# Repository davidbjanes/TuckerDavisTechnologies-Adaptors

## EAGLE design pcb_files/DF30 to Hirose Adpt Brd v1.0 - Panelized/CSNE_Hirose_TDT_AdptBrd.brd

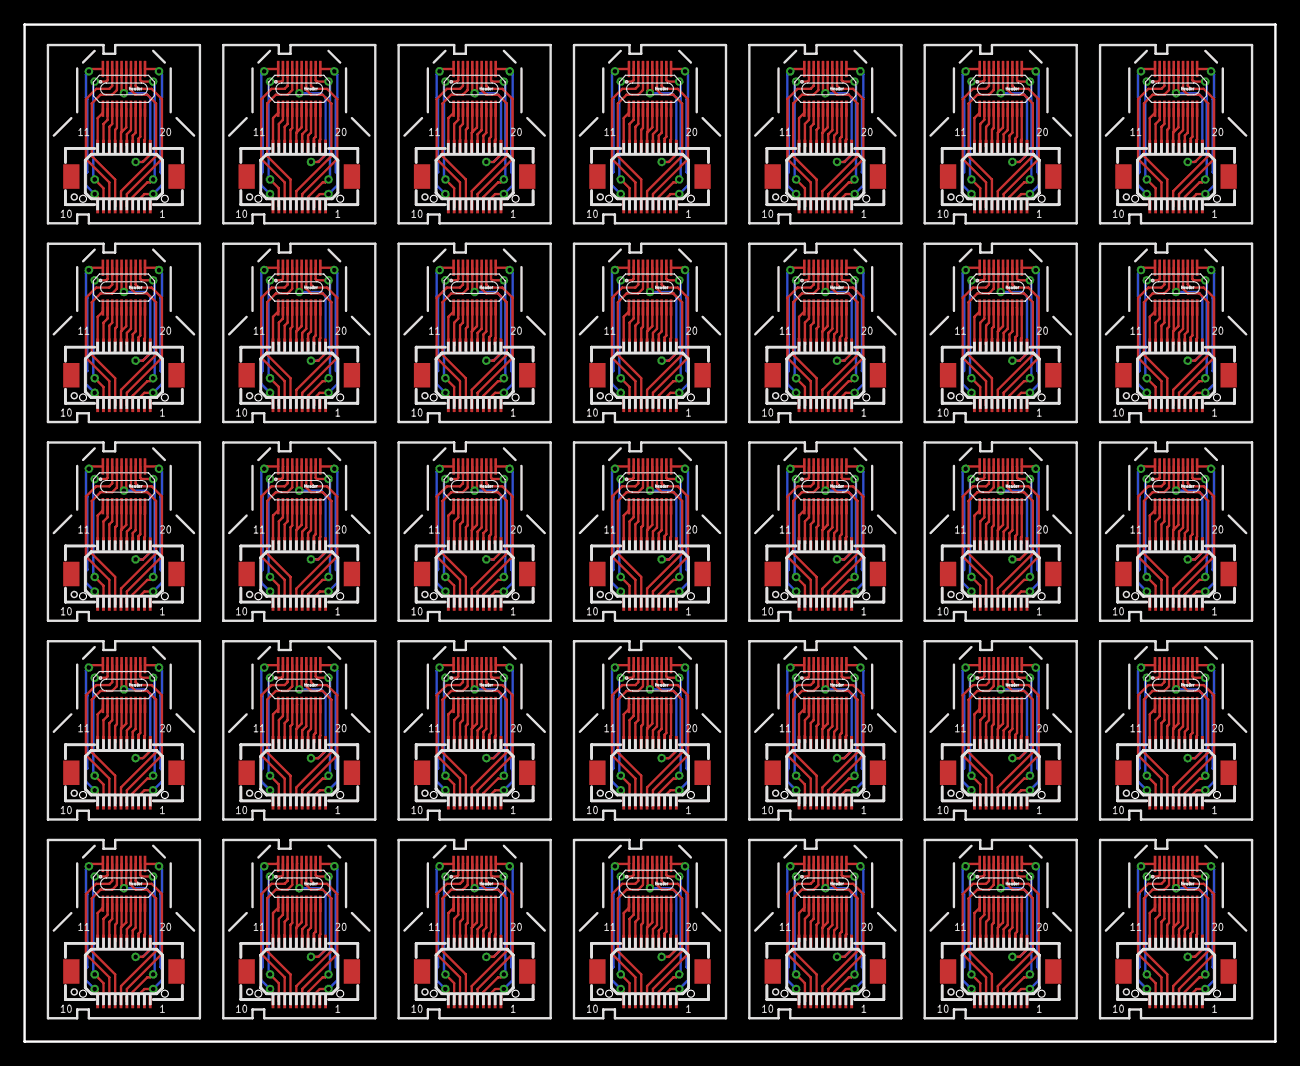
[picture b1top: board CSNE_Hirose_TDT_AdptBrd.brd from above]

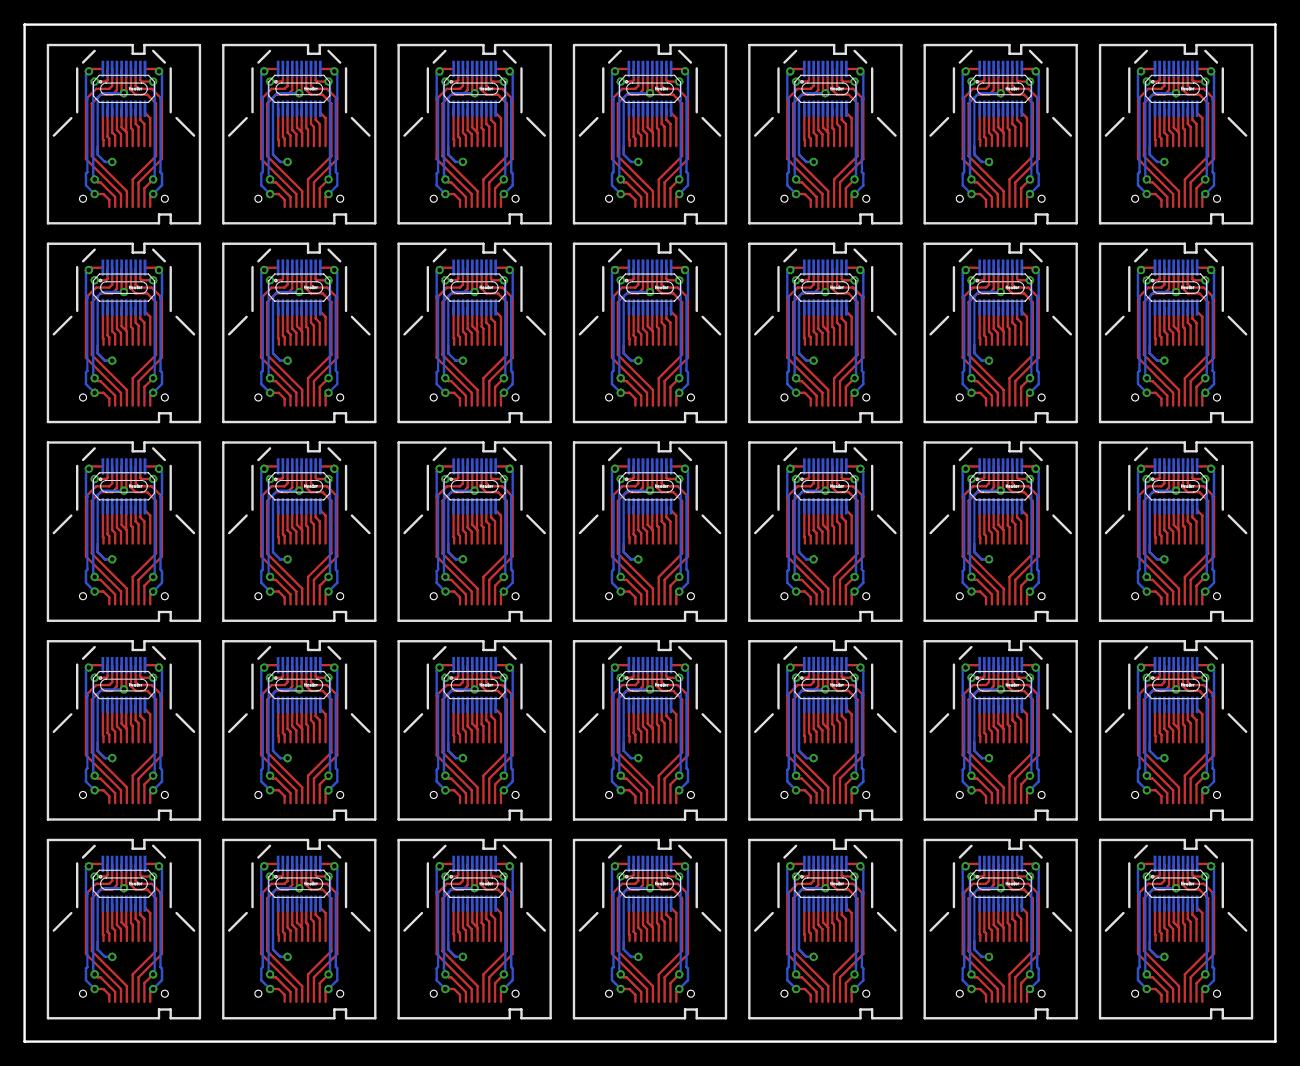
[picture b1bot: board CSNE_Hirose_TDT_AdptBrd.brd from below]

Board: 4 copper layers, 107.0 x 87.0 mm, 105 parts (35 on the bottom side), 630 nets.

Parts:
U$1, U$2, U$4, U$5, U$7, U$8, U$10, U$11, U$13, U$14, U$16, U$17, U$19, U$20, U$22, U$23, U$25, U$26, U$28, U$29, U$31, U$32, U$34, U$35, U$37, U$38, U$40, U$41, U$43, U$44, U$46, U$47, U$49, U$50, U$52, U$53, U$55, U$56, U$58, U$59, U$61, U$62, U$64, U$65, U$67, U$68, U$70, U$71, U$73, U$74, U$76, U$77, U$79, U$80, U$82, U$83, U$85, U$86, U$88, U$89, U$91, U$92, U$94, U$95, U$97, U$98, U$100, U$101, U$103, U$104: DF30_HEADER; DF30FC-20DP-0.4V
U$3, U$6, U$9, U$12, U$15, U$18, U$21, U$24, U$27, U$30, U$33, U$36, U$39, U$42, U$45, U$48, U$51, U$54, U$57, U$60, U$63, U$66, U$69, U$72, U$75, U$78, U$81, U$84, U$87, U$90, U$93, U$96, U$99, U$102, U$105: CON-DF17-20F

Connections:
unnamed: U$1.P$1, U$3.1
unnamed: U$1.P$2, U$3.3
unnamed: U$1.P$3, U$3.5
unnamed: U$1.P$4, U$3.7
unnamed: U$1.P$5, U$1.P$6, U$3.20
unnamed: U$1.P$7, U$3.9
unnamed: U$1.P$8, U$3.11
unnamed: U$1.P$9, U$3.13
unnamed: U$1.P$10, U$3.15
unnamed: U$1.P$11, U$3.18
unnamed: U$1.P$12, U$3.16
unnamed: U$1.P$13, U$3.14
unnamed: U$1.P$14, U$3.12
unnamed: U$5.P$1, U$6.1
unnamed: U$1.P$15, U$1.P$16, U$3.10
unnamed: U$1.P$17, U$3.8
unnamed: U$1.P$18, U$3.6
unnamed: U$1.P$19, U$3.4
unnamed: U$1.P$20, U$3.2
unnamed: U$5.P$2, U$6.3
unnamed: U$5.P$3, U$6.5
unnamed: U$5.P$4, U$6.7
unnamed: U$5.P$5, U$5.P$6, U$6.20
unnamed: U$5.P$7, U$6.9
unnamed: U$5.P$8, U$6.11
unnamed: U$5.P$9, U$6.13
unnamed: U$5.P$10, U$6.15
unnamed: U$5.P$11, U$6.18
unnamed: U$5.P$12, U$6.16
unnamed: U$5.P$13, U$6.14
unnamed: U$5.P$14, U$6.12
unnamed: U$5.P$15, U$5.P$16, U$6.10
unnamed: U$5.P$17, U$6.8
unnamed: U$5.P$18, U$6.6
unnamed: U$5.P$19, U$6.4
unnamed: U$5.P$20, U$6.2
unnamed: U$8.P$1, U$9.1
unnamed: U$8.P$2, U$9.3
unnamed: U$8.P$3, U$9.5
unnamed: U$8.P$4, U$9.7
unnamed: U$8.P$5, U$8.P$6, U$9.20
unnamed: U$8.P$7, U$9.9
unnamed: U$8.P$8, U$9.11
unnamed: U$8.P$9, U$9.13
unnamed: U$8.P$10, U$9.15
unnamed: U$8.P$11, U$9.18
unnamed: U$8.P$12, U$9.16
unnamed: U$8.P$13, U$9.14
unnamed: U$8.P$14, U$9.12
unnamed: U$8.P$15, U$8.P$16, U$9.10
unnamed: U$8.P$17, U$9.8
unnamed: U$8.P$18, U$9.6
unnamed: U$8.P$19, U$9.4
unnamed: U$8.P$20, U$9.2
unnamed: U$11.P$1, U$12.1
unnamed: U$11.P$2, U$12.3
unnamed: U$11.P$3, U$12.5
unnamed: U$11.P$4, U$12.7
unnamed: U$11.P$5, U$11.P$6, U$12.20
unnamed: U$11.P$7, U$12.9
unnamed: U$11.P$8, U$12.11
unnamed: U$11.P$9, U$12.13
unnamed: U$11.P$10, U$12.15
unnamed: U$11.P$11, U$12.18
unnamed: U$11.P$12, U$12.16
unnamed: U$11.P$13, U$12.14
unnamed: U$11.P$14, U$12.12
unnamed: U$11.P$15, U$11.P$16, U$12.10
unnamed: U$11.P$17, U$12.8
unnamed: U$11.P$18, U$12.6
unnamed: U$11.P$19, U$12.4
unnamed: U$11.P$20, U$12.2
unnamed: U$14.P$1, U$15.1
unnamed: U$14.P$2, U$15.3
unnamed: U$14.P$3, U$15.5
unnamed: U$14.P$4, U$15.7
unnamed: U$14.P$5, U$14.P$6, U$15.20
unnamed: U$14.P$7, U$15.9
unnamed: U$14.P$8, U$15.11
unnamed: U$14.P$9, U$15.13
unnamed: U$14.P$10, U$15.15
unnamed: U$14.P$11, U$15.18
unnamed: U$14.P$12, U$15.16
unnamed: U$14.P$13, U$15.14
unnamed: U$14.P$14, U$15.12
unnamed: U$14.P$15, U$14.P$16, U$15.10
unnamed: U$14.P$17, U$15.8
unnamed: U$14.P$18, U$15.6
unnamed: U$14.P$19, U$15.4
unnamed: U$14.P$20, U$15.2
unnamed: U$17.P$1, U$18.1
unnamed: U$17.P$2, U$18.3
unnamed: U$17.P$3, U$18.5
unnamed: U$17.P$4, U$18.7
unnamed: U$17.P$5, U$17.P$6, U$18.20
unnamed: U$17.P$7, U$18.9
unnamed: U$17.P$8, U$18.11
unnamed: U$17.P$9, U$18.13
unnamed: U$17.P$10, U$18.15
unnamed: U$17.P$11, U$18.18
unnamed: U$17.P$12, U$18.16
unnamed: U$17.P$13, U$18.14
unnamed: U$17.P$14, U$18.12
unnamed: U$17.P$15, U$17.P$16, U$18.10
unnamed: U$17.P$17, U$18.8
unnamed: U$17.P$18, U$18.6
unnamed: U$17.P$19, U$18.4
unnamed: U$17.P$20, U$18.2
unnamed: U$20.P$1, U$21.1
unnamed: U$20.P$2, U$21.3
unnamed: U$20.P$3, U$21.5
unnamed: U$20.P$4, U$21.7
unnamed: U$20.P$5, U$20.P$6, U$21.20
unnamed: U$20.P$7, U$21.9
unnamed: U$20.P$8, U$21.11
unnamed: U$20.P$9, U$21.13
unnamed: U$20.P$10, U$21.15
unnamed: U$20.P$11, U$21.18
unnamed: U$20.P$12, U$21.16
unnamed: U$20.P$13, U$21.14
unnamed: U$20.P$14, U$21.12
unnamed: U$20.P$15, U$20.P$16, U$21.10
unnamed: U$20.P$17, U$21.8
unnamed: U$20.P$18, U$21.6
unnamed: U$20.P$19, U$21.4
unnamed: U$20.P$20, U$21.2
unnamed: U$23.P$1, U$24.1
unnamed: U$23.P$2, U$24.3
unnamed: U$23.P$3, U$24.5
unnamed: U$23.P$4, U$24.7
unnamed: U$23.P$5, U$23.P$6, U$24.20
unnamed: U$23.P$7, U$24.9
unnamed: U$23.P$8, U$24.11
unnamed: U$23.P$9, U$24.13
unnamed: U$23.P$10, U$24.15
unnamed: U$23.P$11, U$24.18
unnamed: U$23.P$12, U$24.16
unnamed: U$23.P$13, U$24.14
unnamed: U$23.P$14, U$24.12
unnamed: U$23.P$15, U$23.P$16, U$24.10
unnamed: U$23.P$17, U$24.8
unnamed: U$23.P$18, U$24.6
unnamed: U$23.P$19, U$24.4
unnamed: U$23.P$20, U$24.2
unnamed: U$26.P$1, U$27.1
unnamed: U$26.P$2, U$27.3
unnamed: U$26.P$3, U$27.5
unnamed: U$26.P$4, U$27.7
unnamed: U$26.P$5, U$26.P$6, U$27.20
unnamed: U$26.P$7, U$27.9
unnamed: U$26.P$8, U$27.11
unnamed: U$26.P$9, U$27.13
unnamed: U$26.P$10, U$27.15
unnamed: U$26.P$11, U$27.18
unnamed: U$26.P$12, U$27.16
unnamed: U$26.P$13, U$27.14
unnamed: U$26.P$14, U$27.12
unnamed: U$26.P$15, U$26.P$16, U$27.10
unnamed: U$26.P$17, U$27.8
unnamed: U$26.P$18, U$27.6
unnamed: U$26.P$19, U$27.4
unnamed: U$26.P$20, U$27.2
unnamed: U$29.P$1, U$30.1
unnamed: U$29.P$2, U$30.3
unnamed: U$29.P$3, U$30.5
unnamed: U$29.P$4, U$30.7
unnamed: U$29.P$5, U$29.P$6, U$30.20
unnamed: U$29.P$7, U$30.9
unnamed: U$29.P$8, U$30.11
unnamed: U$29.P$9, U$30.13
unnamed: U$29.P$10, U$30.15
unnamed: U$29.P$11, U$30.18
unnamed: U$29.P$12, U$30.16
unnamed: U$29.P$13, U$30.14
unnamed: U$29.P$14, U$30.12
unnamed: U$29.P$15, U$29.P$16, U$30.10
unnamed: U$29.P$17, U$30.8
unnamed: U$29.P$18, U$30.6
unnamed: U$29.P$19, U$30.4
unnamed: U$29.P$20, U$30.2
unnamed: U$32.P$1, U$33.1
unnamed: U$32.P$2, U$33.3
unnamed: U$32.P$3, U$33.5
unnamed: U$32.P$4, U$33.7
unnamed: U$32.P$5, U$32.P$6, U$33.20
unnamed: U$32.P$7, U$33.9
unnamed: U$32.P$8, U$33.11
unnamed: U$32.P$9, U$33.13
unnamed: U$32.P$10, U$33.15
unnamed: U$32.P$11, U$33.18
unnamed: U$32.P$12, U$33.16
unnamed: U$32.P$13, U$33.14
unnamed: U$32.P$14, U$33.12
unnamed: U$32.P$15, U$32.P$16, U$33.10
unnamed: U$32.P$17, U$33.8
unnamed: U$32.P$18, U$33.6
unnamed: U$32.P$19, U$33.4
unnamed: U$32.P$20, U$33.2
unnamed: U$35.P$1, U$36.1
unnamed: U$35.P$2, U$36.3
unnamed: U$35.P$3, U$36.5
unnamed: U$35.P$4, U$36.7
unnamed: U$35.P$5, U$35.P$6, U$36.20
unnamed: U$35.P$7, U$36.9
unnamed: U$35.P$8, U$36.11
unnamed: U$35.P$9, U$36.13
unnamed: U$35.P$10, U$36.15
unnamed: U$35.P$11, U$36.18
unnamed: U$35.P$12, U$36.16
unnamed: U$35.P$13, U$36.14
unnamed: U$35.P$14, U$36.12
unnamed: U$35.P$15, U$35.P$16, U$36.10
unnamed: U$35.P$17, U$36.8
unnamed: U$35.P$18, U$36.6
unnamed: U$35.P$19, U$36.4
unnamed: U$35.P$20, U$36.2
unnamed: U$38.P$1, U$39.1
unnamed: U$38.P$2, U$39.3
unnamed: U$38.P$3, U$39.5
unnamed: U$38.P$4, U$39.7
unnamed: U$38.P$5, U$38.P$6, U$39.20
unnamed: U$38.P$7, U$39.9
unnamed: U$38.P$8, U$39.11
unnamed: U$38.P$9, U$39.13
unnamed: U$38.P$10, U$39.15
unnamed: U$38.P$11, U$39.18
unnamed: U$38.P$12, U$39.16
unnamed: U$38.P$13, U$39.14
unnamed: U$38.P$14, U$39.12
unnamed: U$38.P$15, U$38.P$16, U$39.10
unnamed: U$38.P$17, U$39.8
unnamed: U$38.P$18, U$39.6
unnamed: U$38.P$19, U$39.4
unnamed: U$38.P$20, U$39.2
unnamed: U$41.P$1, U$42.1
unnamed: U$41.P$2, U$42.3
unnamed: U$41.P$3, U$42.5
unnamed: U$41.P$4, U$42.7
unnamed: U$41.P$5, U$41.P$6, U$42.20
unnamed: U$41.P$7, U$42.9
unnamed: U$41.P$8, U$42.11
unnamed: U$41.P$9, U$42.13
unnamed: U$41.P$10, U$42.15
unnamed: U$41.P$11, U$42.18
unnamed: U$41.P$12, U$42.16
unnamed: U$41.P$13, U$42.14
unnamed: U$41.P$14, U$42.12
unnamed: U$41.P$15, U$41.P$16, U$42.10
unnamed: U$41.P$17, U$42.8
unnamed: U$41.P$18, U$42.6
unnamed: U$41.P$19, U$42.4
unnamed: U$41.P$20, U$42.2
unnamed: U$44.P$1, U$45.1
unnamed: U$44.P$2, U$45.3
unnamed: U$44.P$3, U$45.5
unnamed: U$44.P$4, U$45.7
unnamed: U$44.P$5, U$44.P$6, U$45.20
unnamed: U$44.P$7, U$45.9
unnamed: U$44.P$8, U$45.11
unnamed: U$44.P$9, U$45.13
unnamed: U$44.P$10, U$45.15
unnamed: U$44.P$11, U$45.18
unnamed: U$44.P$12, U$45.16
unnamed: U$44.P$13, U$45.14
unnamed: U$44.P$14, U$45.12
unnamed: U$44.P$15, U$44.P$16, U$45.10
unnamed: U$44.P$17, U$45.8
unnamed: U$44.P$18, U$45.6
unnamed: U$44.P$19, U$45.4
unnamed: U$44.P$20, U$45.2
unnamed: U$47.P$1, U$48.1
unnamed: U$47.P$2, U$48.3
unnamed: U$47.P$3, U$48.5
unnamed: U$47.P$4, U$48.7
unnamed: U$47.P$5, U$47.P$6, U$48.20
unnamed: U$47.P$7, U$48.9
unnamed: U$47.P$8, U$48.11
unnamed: U$47.P$9, U$48.13
unnamed: U$47.P$10, U$48.15
unnamed: U$47.P$11, U$48.18
unnamed: U$47.P$12, U$48.16
unnamed: U$47.P$13, U$48.14
unnamed: U$47.P$14, U$48.12
unnamed: U$47.P$15, U$47.P$16, U$48.10
unnamed: U$47.P$17, U$48.8
unnamed: U$47.P$18, U$48.6
unnamed: U$47.P$19, U$48.4
unnamed: U$47.P$20, U$48.2
unnamed: U$50.P$1, U$51.1
unnamed: U$50.P$2, U$51.3
unnamed: U$50.P$3, U$51.5
unnamed: U$50.P$4, U$51.7
unnamed: U$50.P$5, U$50.P$6, U$51.20
unnamed: U$50.P$7, U$51.9
unnamed: U$50.P$8, U$51.11
unnamed: U$50.P$9, U$51.13
unnamed: U$50.P$10, U$51.15
unnamed: U$50.P$11, U$51.18
unnamed: U$50.P$12, U$51.16
unnamed: U$50.P$13, U$51.14
unnamed: U$50.P$14, U$51.12
unnamed: U$50.P$15, U$50.P$16, U$51.10
unnamed: U$50.P$17, U$51.8
unnamed: U$50.P$18, U$51.6
unnamed: U$50.P$19, U$51.4
unnamed: U$50.P$20, U$51.2
unnamed: U$53.P$1, U$54.1
unnamed: U$53.P$2, U$54.3
unnamed: U$53.P$3, U$54.5
unnamed: U$53.P$4, U$54.7
unnamed: U$53.P$5, U$53.P$6, U$54.20
unnamed: U$53.P$7, U$54.9
unnamed: U$53.P$8, U$54.11
unnamed: U$53.P$9, U$54.13
unnamed: U$53.P$10, U$54.15
unnamed: U$53.P$11, U$54.18
unnamed: U$53.P$12, U$54.16
unnamed: U$53.P$13, U$54.14
unnamed: U$53.P$14, U$54.12
unnamed: U$53.P$15, U$53.P$16, U$54.10
unnamed: U$53.P$17, U$54.8
unnamed: U$53.P$18, U$54.6
unnamed: U$53.P$19, U$54.4
unnamed: U$53.P$20, U$54.2
unnamed: U$56.P$1, U$57.1
unnamed: U$56.P$2, U$57.3
unnamed: U$56.P$3, U$57.5
unnamed: U$56.P$4, U$57.7
unnamed: U$56.P$5, U$56.P$6, U$57.20
unnamed: U$56.P$7, U$57.9
unnamed: U$56.P$8, U$57.11
unnamed: U$56.P$9, U$57.13
unnamed: U$56.P$10, U$57.15
unnamed: U$56.P$11, U$57.18
unnamed: U$56.P$12, U$57.16
unnamed: U$56.P$13, U$57.14
unnamed: U$56.P$14, U$57.12
unnamed: U$56.P$15, U$56.P$16, U$57.10
unnamed: U$56.P$17, U$57.8
unnamed: U$56.P$18, U$57.6
unnamed: U$56.P$19, U$57.4
unnamed: U$56.P$20, U$57.2
unnamed: U$59.P$1, U$60.1
unnamed: U$59.P$2, U$60.3
unnamed: U$59.P$3, U$60.5
unnamed: U$59.P$4, U$60.7
unnamed: U$59.P$5, U$59.P$6, U$60.20
unnamed: U$59.P$7, U$60.9
unnamed: U$59.P$8, U$60.11
unnamed: U$59.P$9, U$60.13
unnamed: U$59.P$10, U$60.15
unnamed: U$59.P$11, U$60.18
unnamed: U$59.P$12, U$60.16
unnamed: U$59.P$13, U$60.14
unnamed: U$59.P$14, U$60.12
unnamed: U$59.P$15, U$59.P$16, U$60.10
unnamed: U$59.P$17, U$60.8
unnamed: U$59.P$18, U$60.6
unnamed: U$59.P$19, U$60.4
unnamed: U$59.P$20, U$60.2
unnamed: U$62.P$1, U$63.1
unnamed: U$62.P$2, U$63.3
unnamed: U$62.P$3, U$63.5
unnamed: U$62.P$4, U$63.7
unnamed: U$62.P$5, U$62.P$6, U$63.20
unnamed: U$62.P$7, U$63.9
unnamed: U$62.P$8, U$63.11
unnamed: U$62.P$9, U$63.13
unnamed: U$62.P$10, U$63.15
unnamed: U$62.P$11, U$63.18
unnamed: U$62.P$12, U$63.16
unnamed: U$62.P$13, U$63.14
unnamed: U$62.P$14, U$63.12
unnamed: U$62.P$15, U$62.P$16, U$63.10
unnamed: U$62.P$17, U$63.8
unnamed: U$62.P$18, U$63.6
unnamed: U$62.P$19, U$63.4
unnamed: U$62.P$20, U$63.2
unnamed: U$65.P$1, U$66.1
unnamed: U$65.P$2, U$66.3
unnamed: U$65.P$3, U$66.5
unnamed: U$65.P$4, U$66.7
unnamed: U$65.P$5, U$65.P$6, U$66.20
unnamed: U$65.P$7, U$66.9
unnamed: U$65.P$8, U$66.11
unnamed: U$65.P$9, U$66.13
unnamed: U$65.P$10, U$66.15
unnamed: U$65.P$11, U$66.18
unnamed: U$65.P$12, U$66.16
unnamed: U$65.P$13, U$66.14
unnamed: U$65.P$14, U$66.12
unnamed: U$65.P$15, U$65.P$16, U$66.10
unnamed: U$65.P$17, U$66.8
unnamed: U$65.P$18, U$66.6
unnamed: U$65.P$19, U$66.4
unnamed: U$65.P$20, U$66.2
unnamed: U$68.P$1, U$69.1
unnamed: U$68.P$2, U$69.3
unnamed: U$68.P$3, U$69.5
unnamed: U$68.P$4, U$69.7
unnamed: U$68.P$5, U$68.P$6, U$69.20
unnamed: U$68.P$7, U$69.9
unnamed: U$68.P$8, U$69.11
unnamed: U$68.P$9, U$69.13
unnamed: U$68.P$10, U$69.15
unnamed: U$68.P$11, U$69.18
unnamed: U$68.P$12, U$69.16
unnamed: U$68.P$13, U$69.14
unnamed: U$68.P$14, U$69.12
unnamed: U$68.P$15, U$68.P$16, U$69.10
unnamed: U$68.P$17, U$69.8
unnamed: U$68.P$18, U$69.6
unnamed: U$68.P$19, U$69.4
unnamed: U$68.P$20, U$69.2
unnamed: U$71.P$1, U$72.1
unnamed: U$71.P$2, U$72.3
unnamed: U$71.P$3, U$72.5
unnamed: U$71.P$4, U$72.7
unnamed: U$71.P$5, U$71.P$6, U$72.20
unnamed: U$71.P$7, U$72.9
unnamed: U$71.P$8, U$72.11
unnamed: U$71.P$9, U$72.13
unnamed: U$71.P$10, U$72.15
unnamed: U$71.P$11, U$72.18
unnamed: U$71.P$12, U$72.16
unnamed: U$71.P$13, U$72.14
unnamed: U$71.P$14, U$72.12
unnamed: U$71.P$15, U$71.P$16, U$72.10
unnamed: U$71.P$17, U$72.8
unnamed: U$71.P$18, U$72.6
unnamed: U$71.P$19, U$72.4
unnamed: U$71.P$20, U$72.2
unnamed: U$74.P$1, U$75.1
unnamed: U$74.P$2, U$75.3
unnamed: U$74.P$3, U$75.5
unnamed: U$74.P$4, U$75.7
unnamed: U$74.P$5, U$74.P$6, U$75.20
unnamed: U$74.P$7, U$75.9
unnamed: U$74.P$8, U$75.11
unnamed: U$74.P$9, U$75.13
unnamed: U$74.P$10, U$75.15
unnamed: U$74.P$11, U$75.18
unnamed: U$74.P$12, U$75.16
unnamed: U$74.P$13, U$75.14
unnamed: U$74.P$14, U$75.12
unnamed: U$74.P$15, U$74.P$16, U$75.10
unnamed: U$74.P$17, U$75.8
unnamed: U$74.P$18, U$75.6
unnamed: U$74.P$19, U$75.4
unnamed: U$74.P$20, U$75.2
unnamed: U$77.P$1, U$78.1
unnamed: U$77.P$2, U$78.3
unnamed: U$77.P$3, U$78.5
unnamed: U$77.P$4, U$78.7
unnamed: U$77.P$5, U$77.P$6, U$78.20
unnamed: U$77.P$7, U$78.9
unnamed: U$77.P$8, U$78.11
unnamed: U$77.P$9, U$78.13
unnamed: U$77.P$10, U$78.15
unnamed: U$77.P$11, U$78.18
unnamed: U$77.P$12, U$78.16
unnamed: U$77.P$13, U$78.14
unnamed: U$77.P$14, U$78.12
unnamed: U$77.P$15, U$77.P$16, U$78.10
unnamed: U$77.P$17, U$78.8
unnamed: U$77.P$18, U$78.6
unnamed: U$77.P$19, U$78.4
unnamed: U$77.P$20, U$78.2
unnamed: U$80.P$1, U$81.1
unnamed: U$80.P$2, U$81.3
unnamed: U$80.P$3, U$81.5
unnamed: U$80.P$4, U$81.7
unnamed: U$80.P$5, U$80.P$6, U$81.20
unnamed: U$80.P$7, U$81.9
unnamed: U$80.P$8, U$81.11
unnamed: U$80.P$9, U$81.13
unnamed: U$80.P$10, U$81.15
unnamed: U$80.P$11, U$81.18
unnamed: U$80.P$12, U$81.16
unnamed: U$80.P$13, U$81.14
unnamed: U$80.P$14, U$81.12
unnamed: U$80.P$15, U$80.P$16, U$81.10
unnamed: U$80.P$17, U$81.8
unnamed: U$80.P$18, U$81.6
unnamed: U$80.P$19, U$81.4
unnamed: U$80.P$20, U$81.2
unnamed: U$83.P$1, U$84.1
unnamed: U$83.P$2, U$84.3
unnamed: U$83.P$3, U$84.5
unnamed: U$83.P$4, U$84.7
unnamed: U$83.P$5, U$83.P$6, U$84.20
unnamed: U$83.P$7, U$84.9
unnamed: U$83.P$8, U$84.11
unnamed: U$83.P$9, U$84.13
unnamed: U$83.P$10, U$84.15
unnamed: U$83.P$11, U$84.18
unnamed: U$83.P$12, U$84.16
unnamed: U$83.P$13, U$84.14
unnamed: U$83.P$14, U$84.12
unnamed: U$83.P$15, U$83.P$16, U$84.10
unnamed: U$83.P$17, U$84.8
unnamed: U$83.P$18, U$84.6
unnamed: U$83.P$19, U$84.4
unnamed: U$83.P$20, U$84.2
unnamed: U$86.P$1, U$87.1
unnamed: U$86.P$2, U$87.3
unnamed: U$86.P$3, U$87.5
unnamed: U$86.P$4, U$87.7
unnamed: U$86.P$5, U$86.P$6, U$87.20
unnamed: U$86.P$7, U$87.9
unnamed: U$86.P$8, U$87.11
unnamed: U$86.P$9, U$87.13
unnamed: U$86.P$10, U$87.15
unnamed: U$86.P$11, U$87.18
unnamed: U$86.P$12, U$87.16
unnamed: U$86.P$13, U$87.14
unnamed: U$86.P$14, U$87.12
unnamed: U$86.P$15, U$86.P$16, U$87.10
unnamed: U$86.P$17, U$87.8
unnamed: U$86.P$18, U$87.6
unnamed: U$86.P$19, U$87.4
unnamed: U$86.P$20, U$87.2
unnamed: U$89.P$1, U$90.1
unnamed: U$89.P$2, U$90.3
unnamed: U$89.P$3, U$90.5
unnamed: U$89.P$4, U$90.7
unnamed: U$89.P$5, U$89.P$6, U$90.20
unnamed: U$89.P$7, U$90.9
unnamed: U$89.P$8, U$90.11
unnamed: U$89.P$9, U$90.13
unnamed: U$89.P$10, U$90.15
unnamed: U$89.P$11, U$90.18
unnamed: U$89.P$12, U$90.16
unnamed: U$89.P$13, U$90.14
unnamed: U$89.P$14, U$90.12
unnamed: U$89.P$15, U$89.P$16, U$90.10
unnamed: U$89.P$17, U$90.8
unnamed: U$89.P$18, U$90.6
unnamed: U$89.P$19, U$90.4
unnamed: U$89.P$20, U$90.2
unnamed: U$92.P$1, U$93.1
unnamed: U$92.P$2, U$93.3
unnamed: U$92.P$3, U$93.5
unnamed: U$92.P$4, U$93.7
unnamed: U$92.P$5, U$92.P$6, U$93.20
unnamed: U$92.P$7, U$93.9
unnamed: U$92.P$8, U$93.11
unnamed: U$92.P$9, U$93.13
unnamed: U$92.P$10, U$93.15
unnamed: U$92.P$11, U$93.18
unnamed: U$92.P$12, U$93.16
unnamed: U$92.P$13, U$93.14
unnamed: U$92.P$14, U$93.12
unnamed: U$92.P$15, U$92.P$16, U$93.10
unnamed: U$92.P$17, U$93.8
unnamed: U$92.P$18, U$93.6
unnamed: U$92.P$19, U$93.4
unnamed: U$92.P$20, U$93.2
unnamed: U$95.P$1, U$96.1
unnamed: U$95.P$2, U$96.3
unnamed: U$95.P$3, U$96.5
unnamed: U$95.P$4, U$96.7
unnamed: U$95.P$5, U$95.P$6, U$96.20
unnamed: U$95.P$7, U$96.9
unnamed: U$95.P$8, U$96.11
unnamed: U$95.P$9, U$96.13
unnamed: U$95.P$10, U$96.15
unnamed: U$95.P$11, U$96.18
unnamed: U$95.P$12, U$96.16
unnamed: U$95.P$13, U$96.14
unnamed: U$95.P$14, U$96.12
unnamed: U$95.P$15, U$95.P$16, U$96.10
unnamed: U$95.P$17, U$96.8
unnamed: U$95.P$18, U$96.6
unnamed: U$95.P$19, U$96.4
unnamed: U$95.P$20, U$96.2
unnamed: U$98.P$1, U$99.1
unnamed: U$98.P$2, U$99.3
unnamed: U$98.P$3, U$99.5
unnamed: U$98.P$4, U$99.7
unnamed: U$98.P$5, U$98.P$6, U$99.20
unnamed: U$98.P$7, U$99.9
unnamed: U$98.P$8, U$99.11
unnamed: U$98.P$9, U$99.13
unnamed: U$98.P$10, U$99.15
unnamed: U$98.P$11, U$99.18
unnamed: U$98.P$12, U$99.16
unnamed: U$98.P$13, U$99.14
unnamed: U$98.P$14, U$99.12
unnamed: U$98.P$15, U$98.P$16, U$99.10
unnamed: U$98.P$17, U$99.8
unnamed: U$98.P$18, U$99.6
unnamed: U$98.P$19, U$99.4
unnamed: U$98.P$20, U$99.2
unnamed: U$101.P$1, U$102.1
unnamed: U$101.P$2, U$102.3
unnamed: U$101.P$3, U$102.5
unnamed: U$101.P$4, U$102.7
unnamed: U$101.P$5, U$101.P$6, U$102.20
unnamed: U$101.P$7, U$102.9
unnamed: U$101.P$8, U$102.11
unnamed: U$101.P$9, U$102.13
unnamed: U$101.P$10, U$102.15
unnamed: U$101.P$11, U$102.18
unnamed: U$101.P$12, U$102.16
unnamed: U$101.P$13, U$102.14
unnamed: U$101.P$14, U$102.12
unnamed: U$101.P$15, U$101.P$16, U$102.10
unnamed: U$101.P$17, U$102.8
unnamed: U$101.P$18, U$102.6
unnamed: U$101.P$19, U$102.4
unnamed: U$101.P$20, U$102.2
unnamed: U$104.P$1, U$105.1
unnamed: U$104.P$2, U$105.3
unnamed: U$104.P$3, U$105.5
unnamed: U$104.P$4, U$105.7
unnamed: U$104.P$5, U$104.P$6, U$105.20
unnamed: U$104.P$7, U$105.9
unnamed: U$104.P$8, U$105.11
unnamed: U$104.P$9, U$105.13
unnamed: U$104.P$10, U$105.15
unnamed: U$104.P$11, U$105.18
unnamed: U$104.P$12, U$105.16
unnamed: U$104.P$13, U$105.14
unnamed: U$104.P$14, U$105.12
unnamed: U$104.P$15, U$104.P$16, U$105.10
unnamed: U$104.P$17, U$105.8
unnamed: U$104.P$18, U$105.6
unnamed: U$104.P$19, U$105.4
unnamed: U$104.P$20, U$105.2

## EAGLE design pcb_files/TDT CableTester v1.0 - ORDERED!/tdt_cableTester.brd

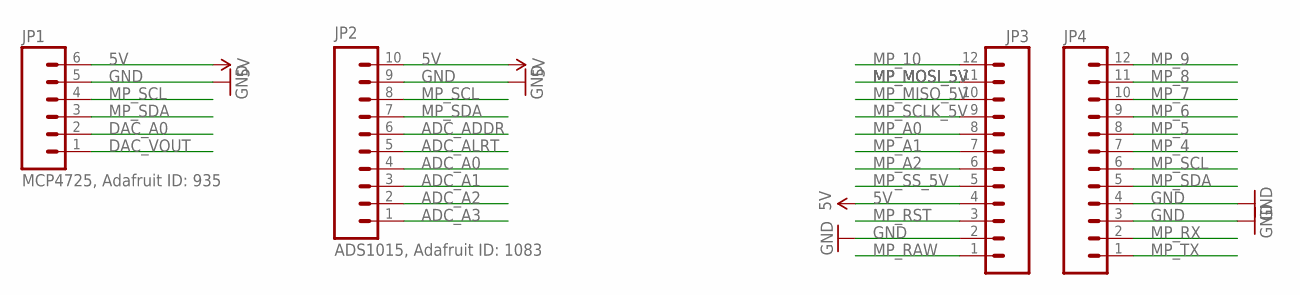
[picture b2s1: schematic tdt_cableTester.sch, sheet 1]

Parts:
JP1: MCP4725, Adafruit ID: 935; 1X06
JP2: ADS1015, Adafruit ID: 1083; 1X10
JP3, JP4: M12PTH; 1X12

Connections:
5V: JP1.6, JP2.10, JP3.4; also elsewhere on the board
ADC_A0: JP2.4
ADC_A1: JP2.3; also elsewhere on the board
ADC_A2: JP2.2; also elsewhere on the board
ADC_A3: JP2.1; also elsewhere on the board
ADC_ADDR: JP2.6
ADC_ALRT: JP2.5
DAC_A0: JP1.2
DAC_VOUT: JP1.1; also elsewhere on the board
GND: JP1.5, JP2.9, JP3.2, JP4.3, JP4.4; also elsewhere on the board
MP_4: JP4.7; also elsewhere on the board
MP_5: JP4.8; also elsewhere on the board
MP_6: JP4.9; also elsewhere on the board
MP_7: JP4.10; also elsewhere on the board
MP_8: JP4.11; also elsewhere on the board
MP_9: JP4.12; also elsewhere on the board
MP_10: JP3.12; also elsewhere on the board
MP_A0: JP3.8; also elsewhere on the board
MP_A1: JP3.7; also elsewhere on the board
MP_A2: JP3.6; also elsewhere on the board
MP_MISO_5V: JP3.10; also elsewhere on the board
MP_MOSI_5V: JP3.11; also elsewhere on the board
MP_RAW: JP3.1
MP_RST: JP3.3
MP_RX: JP4.2
MP_SCL: JP1.4, JP2.8, JP4.6
MP_SCLK_5V: JP3.9; also elsewhere on the board
MP_SDA: JP1.3, JP2.7, JP4.5
MP_SS_5V: JP3.5; also elsewhere on the board
MP_TX: JP4.1

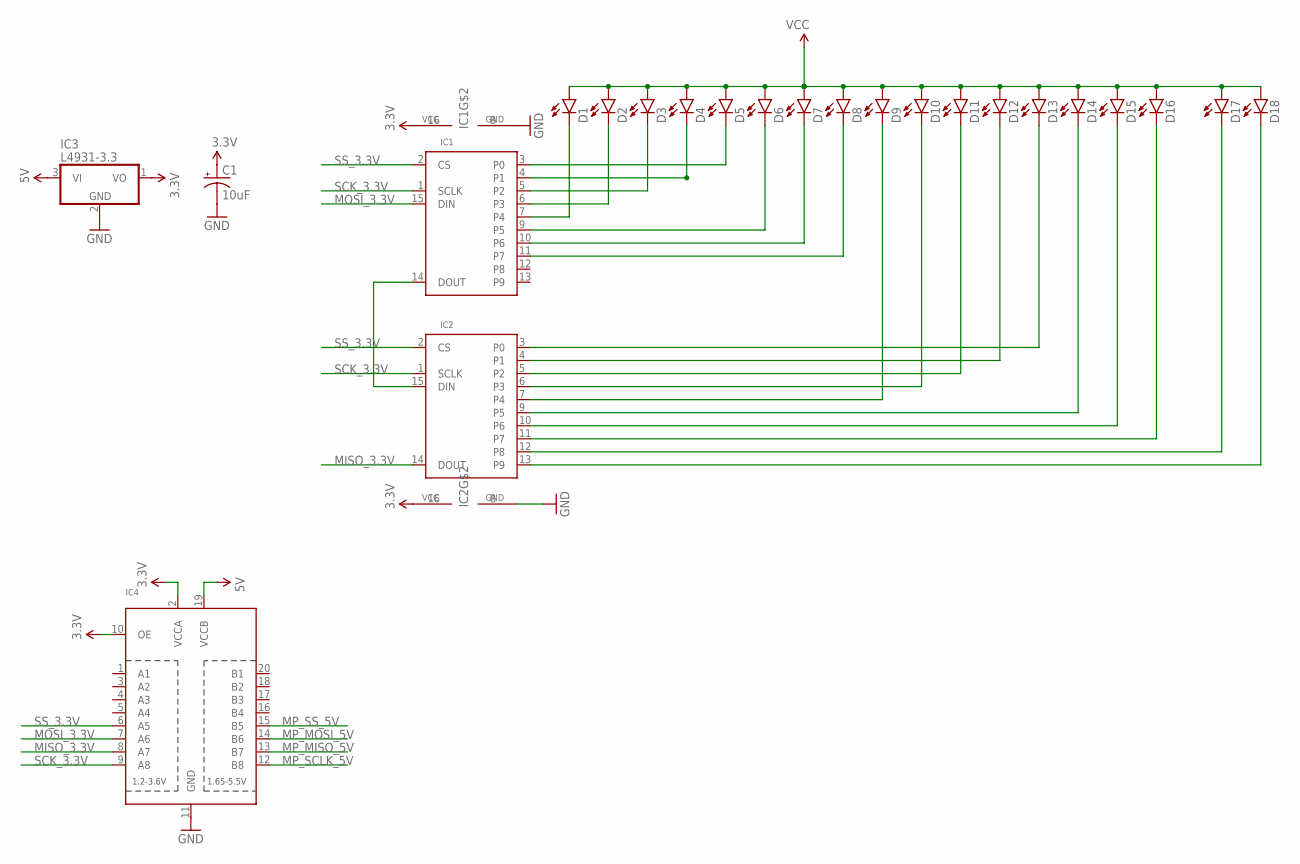
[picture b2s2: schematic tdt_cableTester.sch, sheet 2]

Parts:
C1: 10uF; CPOL-RADIAL-10UF-25V
D1, D2, D3, D4, D5, D6, D7, D8, D9, D10, D11, D12, D13, D14, D15, D16, D17, D18: LED1206; LED-1206
IC1, IC2: MAX6966AEE; QSOP16
IC3: L4931-3.3; TO92
IC4: TXB0108PWR; TSSOP20

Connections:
3.3V: C1.1 (+), IC1.16 (VCC), IC2.16 (VCC), IC3.1 (VO), IC4.2 (VCCA), IC4.10 (OE)
5V: IC3.3 (VI), IC4.19 (VCCB); also elsewhere on the board
DOUT_3.3V: IC1.14 (DOUT), IC2.15 (DIN)
GND: C1.2 (-), IC1.8 (GND), IC2.8 (GND), IC3.2 (GND), IC4.11 (GND); also elsewhere on the board
MISO_3.3V: IC2.14 (DOUT), IC4.8 (A7)
MOSI_3.3V: IC1.15 (DIN), IC4.7 (A6)
MP_MISO_5V: IC4.13 (B7); also elsewhere on the board
MP_MOSI_5V: IC4.14 (B6); also elsewhere on the board
MP_SCLK_5V: IC4.12 (B8); also elsewhere on the board
MP_SS_5V: IC4.15 (B5); also elsewhere on the board
unnamed: D9.C, IC2.7 (P4)
unnamed: D10.C, IC2.6 (P3)
unnamed: D11.C, IC2.5 (P2)
unnamed: D12.C, IC2.4 (P1)
unnamed: D13.C, IC2.3 (P0)
unnamed: D14.C, IC2.9 (P5)
unnamed: D5.C, IC1.3 (P0)
unnamed: D3.C, IC1.5 (P2)
unnamed: D2.C, IC1.6 (P3)
unnamed: D1.C, IC1.7 (P4)
unnamed: D6.C, IC1.9 (P5)
unnamed: D7.C, IC1.10 (P6)
unnamed: D8.C, IC1.11 (P7)
unnamed: D4.C, IC1.4 (P1)
unnamed: D16.C, IC2.11 (P7)
unnamed: D18.C, IC2.13 (P9)
unnamed: D15.C, IC2.10 (P6)
unnamed: D17.C, IC2.12 (P8)
SCK_3.3V: IC1.1 (SCLK), IC2.1 (SCLK), IC4.9 (A8)
SS_3.3V: IC1.2 (CS), IC2.2 (CS), IC4.6 (A5)
VCC: D1.A, D2.A, D3.A, D4.A, D5.A, D6.A, D7.A, D8.A, D9.A, D10.A, D11.A, D12.A, D13.A, D14.A, D15.A, D16.A, D17.A, D18.A

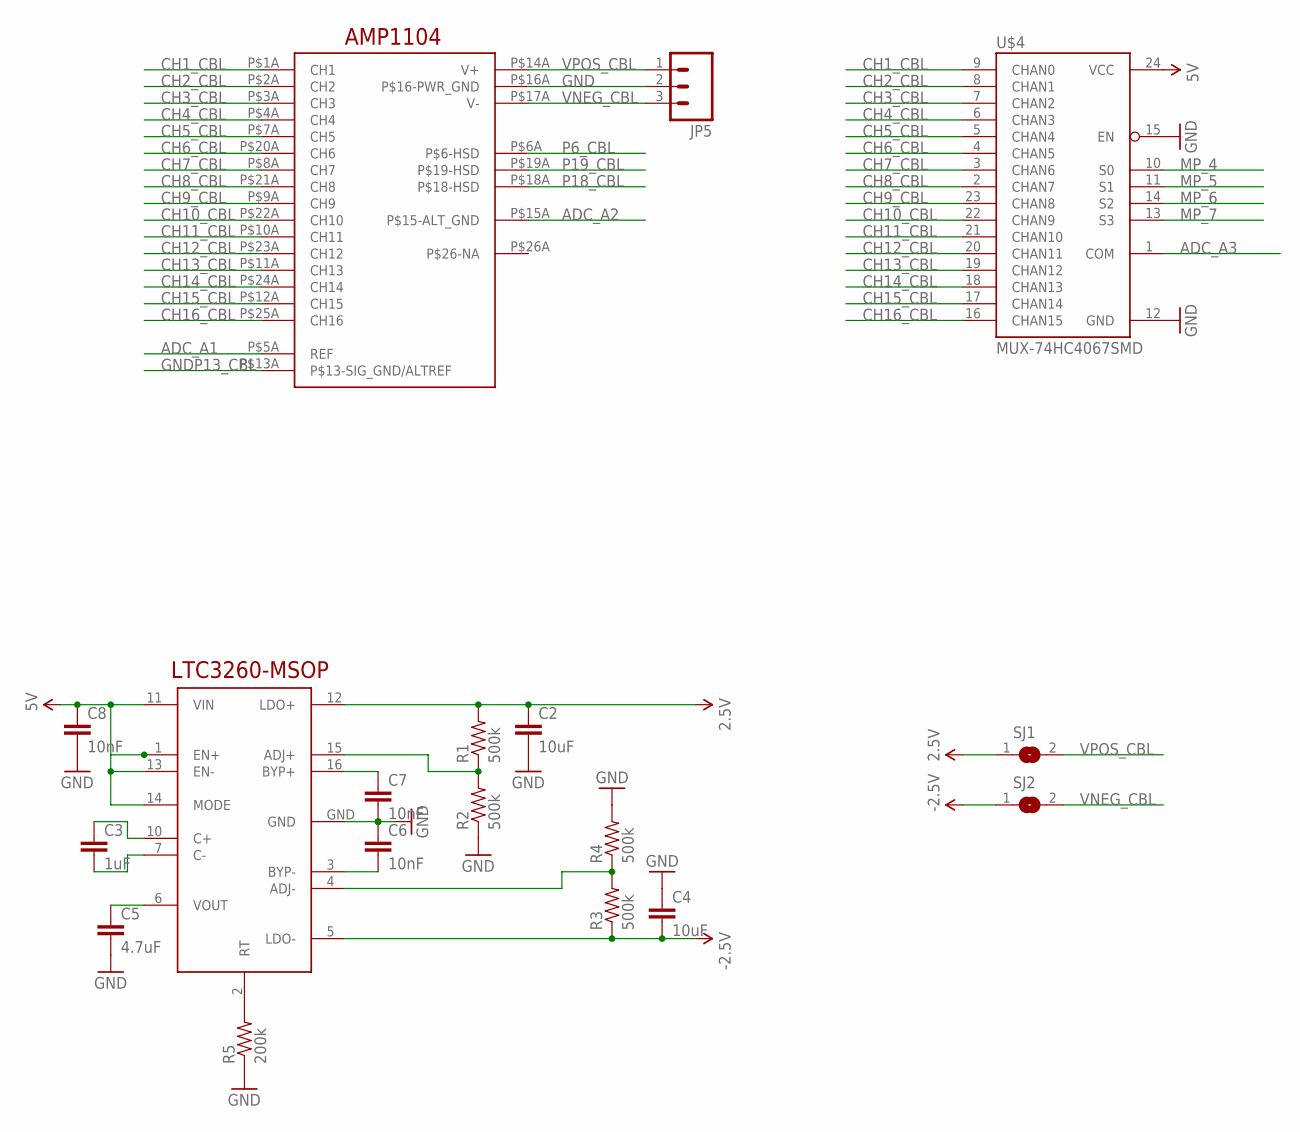
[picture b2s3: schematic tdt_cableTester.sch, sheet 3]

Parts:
C2, C4: 10uF; 0805
C3: 1uF; 0805
C5: 4.7uF; 0805
C6, C7, C8: 10nF; 0805
JP5: M03PTH; 1X03
R1, R2, R3, R4: 500k; 0805
R5: 200k; 0805
SJ1, SJ2: SJ
U$3: AMP1104
U$4: MUX-74HC4067SMD; SSOP24
U$7: LTC3260-MSOP; MSOP16

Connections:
2.5V: C2.1, R1.2, SJ1.1, U$7.12 (LDO+)
5V: C8.1, U$4.24 (VCC), U$7.1 (EN+), U$7.11 (VIN), U$7.13 (EN-), U$7.14 (MODE); also elsewhere on the board
-2.5V: C4.2, R3.1, SJ2.1, U$7.5 (LDO-)
ADC_A1: U$3.P$5A (REF); also elsewhere on the board
ADC_A2: U$3.P$15A (P$15-ALT_GND); also elsewhere on the board
ADC_A3: U$4.1 (COM); also elsewhere on the board
CH1_CBL: U$3.P$1A (CH1), U$4.9 (CHAN0)
CH2_CBL: U$3.P$2A (CH2), U$4.8 (CHAN1)
CH3_CBL: U$3.P$3A (CH3), U$4.7 (CHAN2)
CH4_CBL: U$3.P$4A (CH4), U$4.6 (CHAN3)
CH5_CBL: U$3.P$7A (CH5), U$4.5 (CHAN4)
CH6_CBL: U$3.P$20A (CH6), U$4.4 (CHAN5)
CH7_CBL: U$3.P$8A (CH7), U$4.3 (CHAN6)
CH8_CBL: U$3.P$21A (CH8), U$4.2 (CHAN7)
CH9_CBL: U$3.P$9A (CH9), U$4.23 (CHAN8)
CH10_CBL: U$3.P$22A (CH10), U$4.22 (CHAN9)
CH11_CBL: U$3.P$10A (CH11), U$4.21 (CHAN10)
CH12_CBL: U$3.P$23A (CH12), U$4.20 (CHAN11)
CH13_CBL: U$3.P$11A (CH13), U$4.19 (CHAN12)
CH14_CBL: U$3.P$24A (CH14), U$4.18 (CHAN13)
CH15_CBL: U$3.P$12A (CH15), U$4.17 (CHAN14)
CH16_CBL: U$3.P$25A (CH16), U$4.16 (CHAN15)
GND: C2.2, C4.1, C5.2, C6.1, C7.2, C8.2, JP5.2, R2.1, R4.2, R5.1, U$3.P$16A (P$16-PWR_GND), U$4.12 (GND), U$4.15 (EN), U$7.GND; also elsewhere on the board
GNDP13_CBL: U$3.P$13A (P$13-SIG_GND/ALTREF)
MP_4: U$4.10 (S0); also elsewhere on the board
MP_5: U$4.11 (S1); also elsewhere on the board
MP_6: U$4.14 (S2); also elsewhere on the board
MP_7: U$4.13 (S3); also elsewhere on the board
unnamed: R1.1, R2.2, U$7.15 (ADJ+)
unnamed: C6.2, U$7.3 (BYP-)
unnamed: R5.2, U$7.2 (RT)
unnamed: C7.1, U$7.16 (BYP+)
unnamed: R3.2, R4.1, U$7.4 (ADJ-)
unnamed: C3.1, U$7.10 (C+)
unnamed: C3.2, U$7.7 (C-)
unnamed: C5.1, U$7.6 (VOUT)
P6_CBL: U$3.P$6A (P$6-HSD)
P18_CBL: U$3.P$18A (P$18-HSD)
P19_CBL: U$3.P$19A (P$19-HSD)
VNEG_CBL: JP5.3, SJ2.2, U$3.P$17A (V-)
VPOS_CBL: JP5.1, SJ1.2, U$3.P$14A (V+)

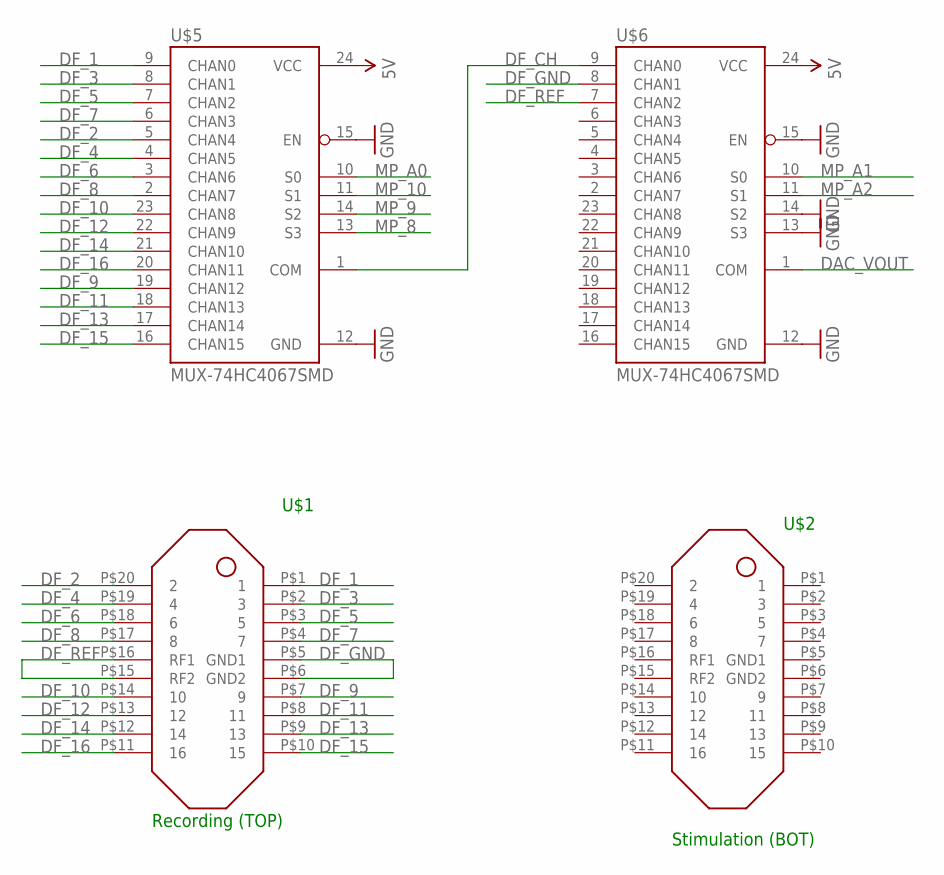
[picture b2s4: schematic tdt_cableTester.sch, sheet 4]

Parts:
U$1, U$2: DF30_HEADER; DF30FC-20DP-0.4V
U$5, U$6: MUX-74HC4067SMD; SSOP24

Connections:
5V: U$5.24 (VCC), U$6.24 (VCC); also elsewhere on the board
DAC_VOUT: U$6.1 (COM); also elsewhere on the board
DF_1: U$1.P$1 (1), U$5.9 (CHAN0)
DF_2: U$1.P$20 (2), U$5.5 (CHAN4)
DF_3: U$1.P$2 (3), U$5.8 (CHAN1)
DF_4: U$1.P$19 (4), U$5.4 (CHAN5)
DF_5: U$1.P$3 (5), U$5.7 (CHAN2)
DF_6: U$1.P$18 (6), U$5.3 (CHAN6)
DF_7: U$1.P$4 (7), U$5.6 (CHAN3)
DF_8: U$1.P$17 (8), U$5.2 (CHAN7)
DF_9: U$1.P$7 (9), U$5.19 (CHAN12)
DF_10: U$1.P$14 (10), U$5.23 (CHAN8)
DF_11: U$1.P$8 (11), U$5.18 (CHAN13)
DF_12: U$1.P$13 (12), U$5.22 (CHAN9)
DF_13: U$1.P$9 (13), U$5.17 (CHAN14)
DF_14: U$1.P$12 (14), U$5.21 (CHAN10)
DF_15: U$1.P$10 (15), U$5.16 (CHAN15)
DF_16: U$1.P$11 (16), U$5.20 (CHAN11)
DF_CH: U$5.1 (COM), U$6.9 (CHAN0)
DF_GND: U$1.P$5 (GND1), U$1.P$6 (GND2), U$6.8 (CHAN1)
DF_REF: U$1.P$15 (RF2), U$1.P$16 (RF1), U$6.7 (CHAN2)
GND: U$5.12 (GND), U$5.15 (EN), U$6.12 (GND), U$6.13 (S3), U$6.14 (S2), U$6.15 (EN); also elsewhere on the board
MP_8: U$5.13 (S3); also elsewhere on the board
MP_9: U$5.14 (S2); also elsewhere on the board
MP_10: U$5.11 (S1); also elsewhere on the board
MP_A0: U$5.10 (S0); also elsewhere on the board
MP_A1: U$6.10 (S0); also elsewhere on the board
MP_A2: U$6.11 (S1); also elsewhere on the board

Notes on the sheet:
U$2
U$1
Recording (TOP)
Stimulation (BOT)

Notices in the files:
parts and their libraries:
SparkFun-AnalogIC: Licensing:Creative Commons ShareAlike 4.0 International - https://creativecommons.org/licenses/by-sa/4.0
